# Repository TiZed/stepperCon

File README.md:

<b>stepperCon</b> is a PIC18F46K22 based stepper motor controller.

It was created as an exercise in controlling stepper motors for a CNC project. The board and firmware were designed to drive a L298P driver but can probably be adapted to other drivers.

'master' branch - Has hybrid PWM-analog current control. <br />
'a2d_pid' branch - Has the ADC PI current control, not stable yet.

Some of the feature of this project:
- Micro-stepping, selectable up to 16 micro-steps.
- Current limiting.
- I2C interface for configuration.
- Two indicator LEDs.

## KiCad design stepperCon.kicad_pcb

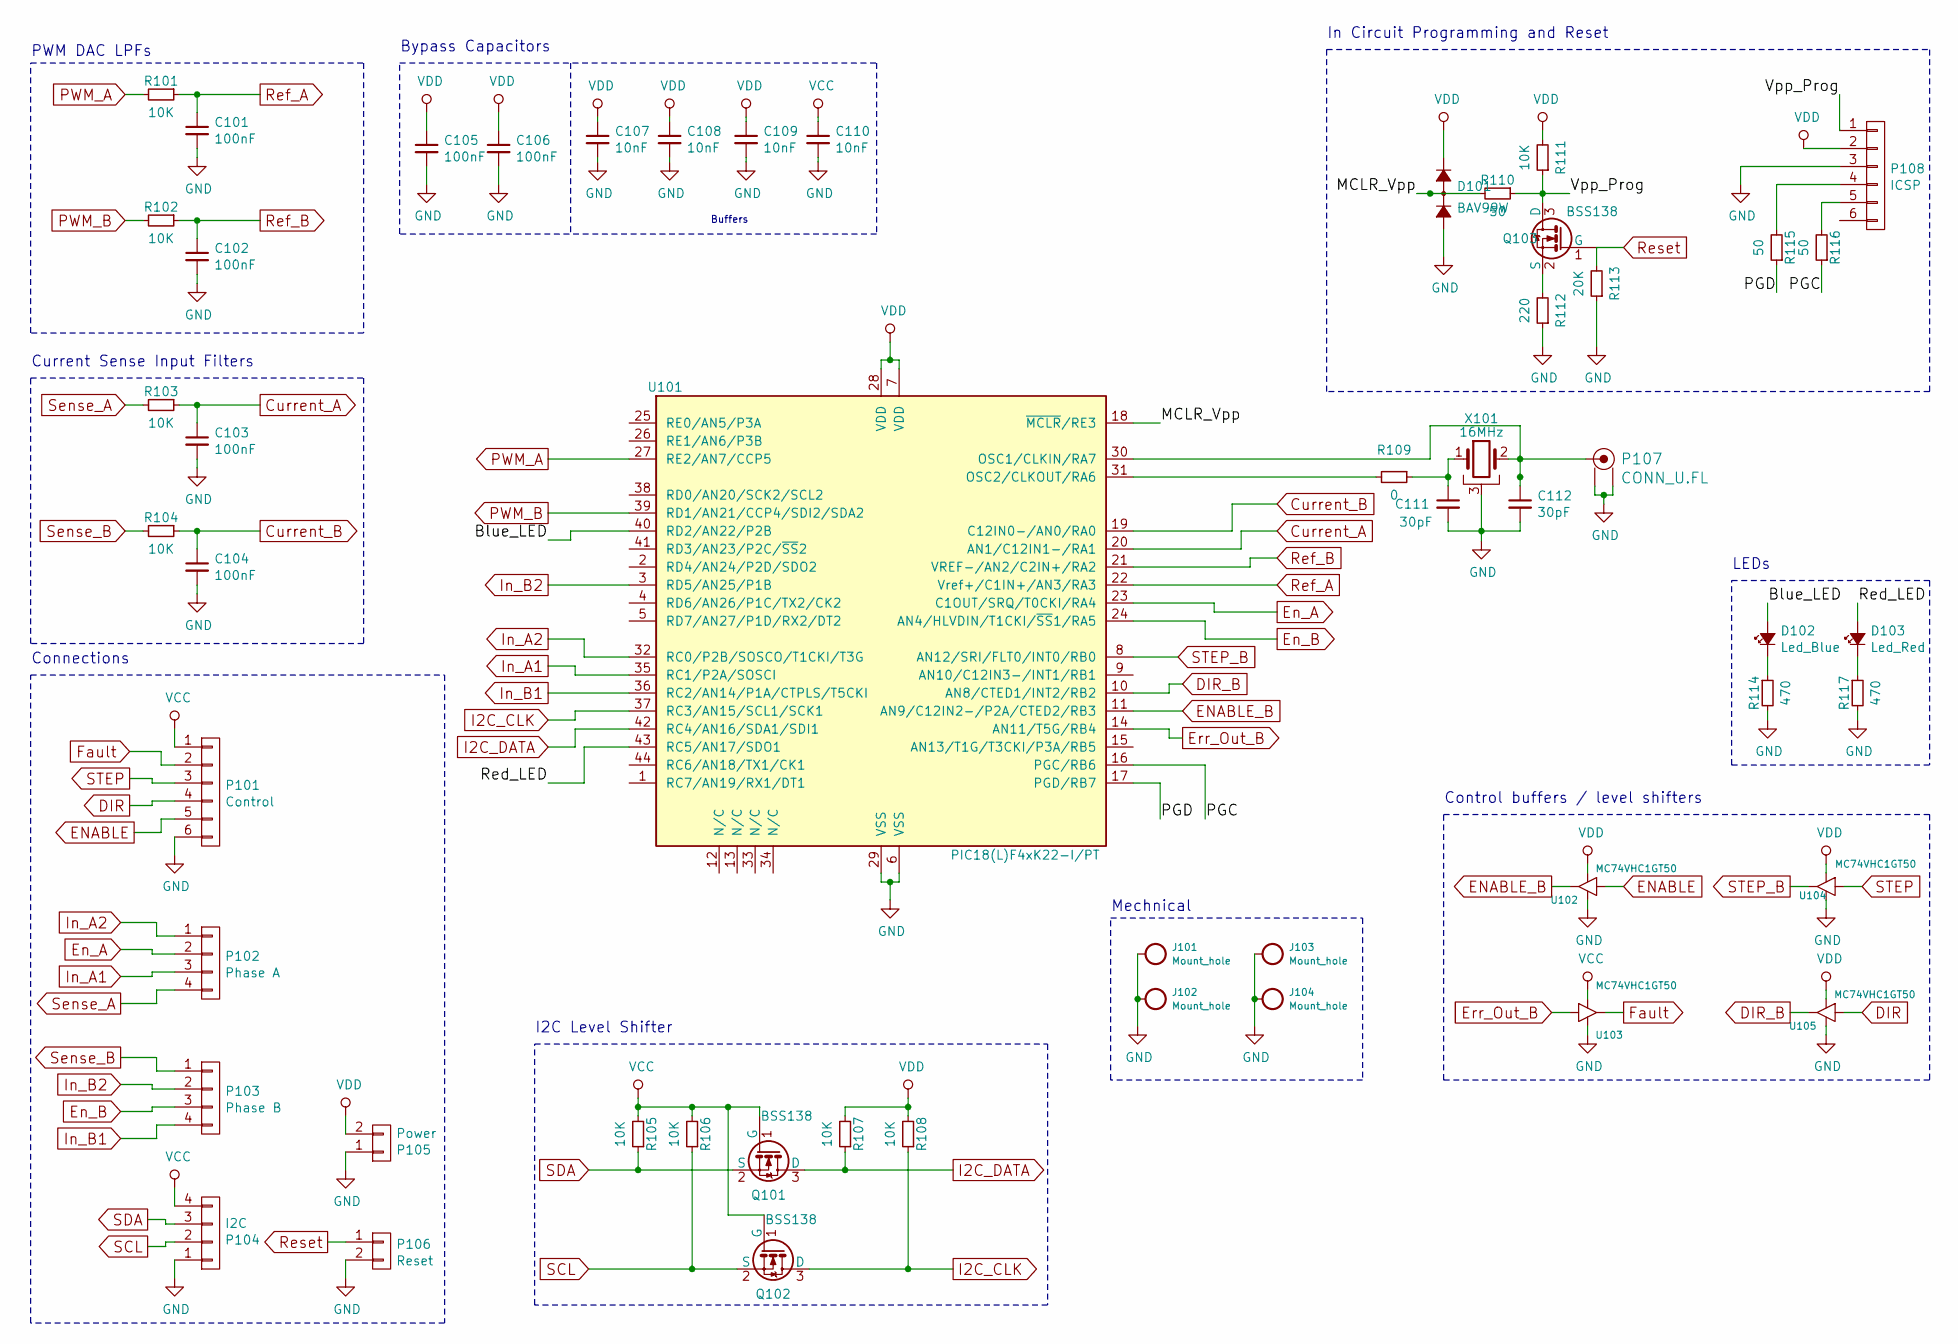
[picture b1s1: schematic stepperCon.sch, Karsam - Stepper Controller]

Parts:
C101, C102, C103, C104, C105, C106: 100nF; C_0603
C107, C108, C109, C110: 10nF; C_0603
C111, C112: 30pF; C_0603
D101: BAV99W; SOT-323
D102: Led_Blue; LED_0805
D103: Led_Red; LED_0805
J101, J102, J103, J104: Mount_hole; MountingHole_3.2mm_M3_Pad
P101: Control; Socket_Strip_Straight_1x06
P102: Phase A; Socket_Strip_Straight_1x04
P103: Phase B; Socket_Strip_Straight_1x04
P104: I2C; Socket_Strip_Straight_1x04
P105: Power; Socket_Strip_Straight_1x02
P106: Reset; Socket_Strip_Straight_1x02
P107: CONN_U.FL; UFL
P108: ICSP
Q101, Q102, Q103: BSS138; SOT-323
R101, R102, R103, R104, R105, R106, R107, R108, R111: 10K; R_0603
R109: 0; R_0603
R110, R115, R116: 50; R_0603
R112: 220; R_0603
R113: 20K; R_0603
R114, R117: 470; R_0603
U101: PIC18(L)F4xK22-I/PT; TQFP-44_10x10mm_Pitch0.8mm
U102, U103, U104, U105: MC74VHC1GT50; SOT-353
X101: 16MHz

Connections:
/Blue_LED: D102.2 (A), U101.40 (RD2/AN22/P2B)
/MCLR_Vpp: D101.3 (AK), R110.2, U101.18 (~MCLR~/RE3)
/PGC: R116.1, U101.16 (PGC/RB6)
/PGD: R115.1, U101.17 (PGD/RB7)
/Red_LED: D103.2 (A), U101.43 (RC5/AN17/SDO1)
/Vpp_Prog: P108.1, Q103.3 (D), R110.1, R111.1
Current_A: C103.1, R103.1, U101.20 (AN1/C12IN1-/RA1)
Current_B: C104.1, R104.1, U101.19 (C12IN0-/AN0/RA0)
DIR: P101.4, U105.2 (IN_A)
DIR_B: U101.10 (AN8/CTED1/INT2/RB2), U105.4 (OUT_Y)
ENABLE: P101.5, U102.2 (IN_A)
ENABLE_B: U101.11 (AN9/C12IN2-/P2A/CTED2/RB3), U102.4 (OUT_Y)
En_A: P102.2, U101.23 (C1OUT/SRQ/T0CKI/RA4)
En_B: P103.3, U101.24 (AN4/HLVDIN/T1CKI/~SS~1/RA5)
Err_Out_B: U101.14 (AN11/T5G/RB4), U103.2 (IN_A)
Fault: P101.2, U103.4 (OUT_Y)
GND: C101.2, C102.2, C103.2, C104.2, C105.2, C106.2, C107.2, C108.2, C109.2, C110.2, C111.2, C112.2, D101.1 (K), J101.1, J102.1, J103.1, J104.1, P101.6, P104.1, P105.1, P106.2, P107.2, P107.3, P108.3, R112.1, R113.1, R114.2, R117.2, U101.6 (VSS), U101.29 (VSS), U102.3 (GND), U103.3 (GND), U104.3 (GND), U105.3 (GND), X101.3
I2C_CLK: Q102.3 (D), R108.1, U101.37 (RC3/AN15/SCL1/SCK1)
I2C_DATA: Q101.3 (D), R107.1, U101.42 (RC4/AN16/SDA1/SDI1)
In_A1: P102.3, U101.35 (RC1/P2A/SOSCI)
In_A2: P102.1, U101.32 (RC0/P2B/SOSCO/T1CKI/T3G)
In_B1: P103.4, U101.36 (RC2/AN14/P1A/CTPLS/T5CKI)
In_B2: P103.2, U101.3 (RD5/AN25/P1B)
unnamed: C111.1, R109.1, X101.1
unnamed: C112.1, P107.1, U101.30 (OSC1/CLKIN/RA7), X101.2
unnamed: D102.1 (K), R114.1
unnamed: D103.1 (K), R117.1
unnamed: P108.4, R115.2
unnamed: P108.5, R116.2
unnamed: Q103.2 (S), R112.2
unnamed: R109.2, U101.31 (OSC2/CLKOUT/RA6)
PWM_A: R101.2, U101.27 (RE2/AN7/CCP5)
PWM_B: R102.2, U101.39 (RD1/AN21/CCP4/SDI2/SDA2)
Ref_A: C101.1, R101.1, U101.22 (Vref+/C1IN+/AN3/RA3)
Ref_B: C102.1, R102.1, U101.21 (VREF-/AN2/C2IN+/RA2)
Reset: P106.1, Q103.1 (G), R113.2
SCL: P104.2, Q102.2 (S), R106.1
SDA: P104.3, Q101.2 (S), R105.1
STEP: P101.3, U104.2 (IN_A)
STEP_B: U101.8 (AN12/SRI/FLT0/INT0/RB0), U104.4 (OUT_Y)
Sense_A: P102.4, R103.2
Sense_B: P103.1, R104.2
VCC: C110.1, P101.1, P104.4, Q101.1 (G), Q102.1 (G), R105.2, R106.2, U103.5 (VCC)
VDD: C105.1, C106.1, C107.1, C108.1, C109.1, D101.2 (A), P105.2, P108.2, R107.2, R108.2, R111.2, U101.7 (VDD), U101.28 (VDD), U102.5 (VCC), U104.5 (VCC), U105.5 (VCC)

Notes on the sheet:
I2C Level Shifter
PWM DAC LPFs
Current Sense Input Filters
Mechnical
Connections
Control buffers / level shifters
Bypass Capacitors
Buffers
LEDs
In Circuit Programming and Reset

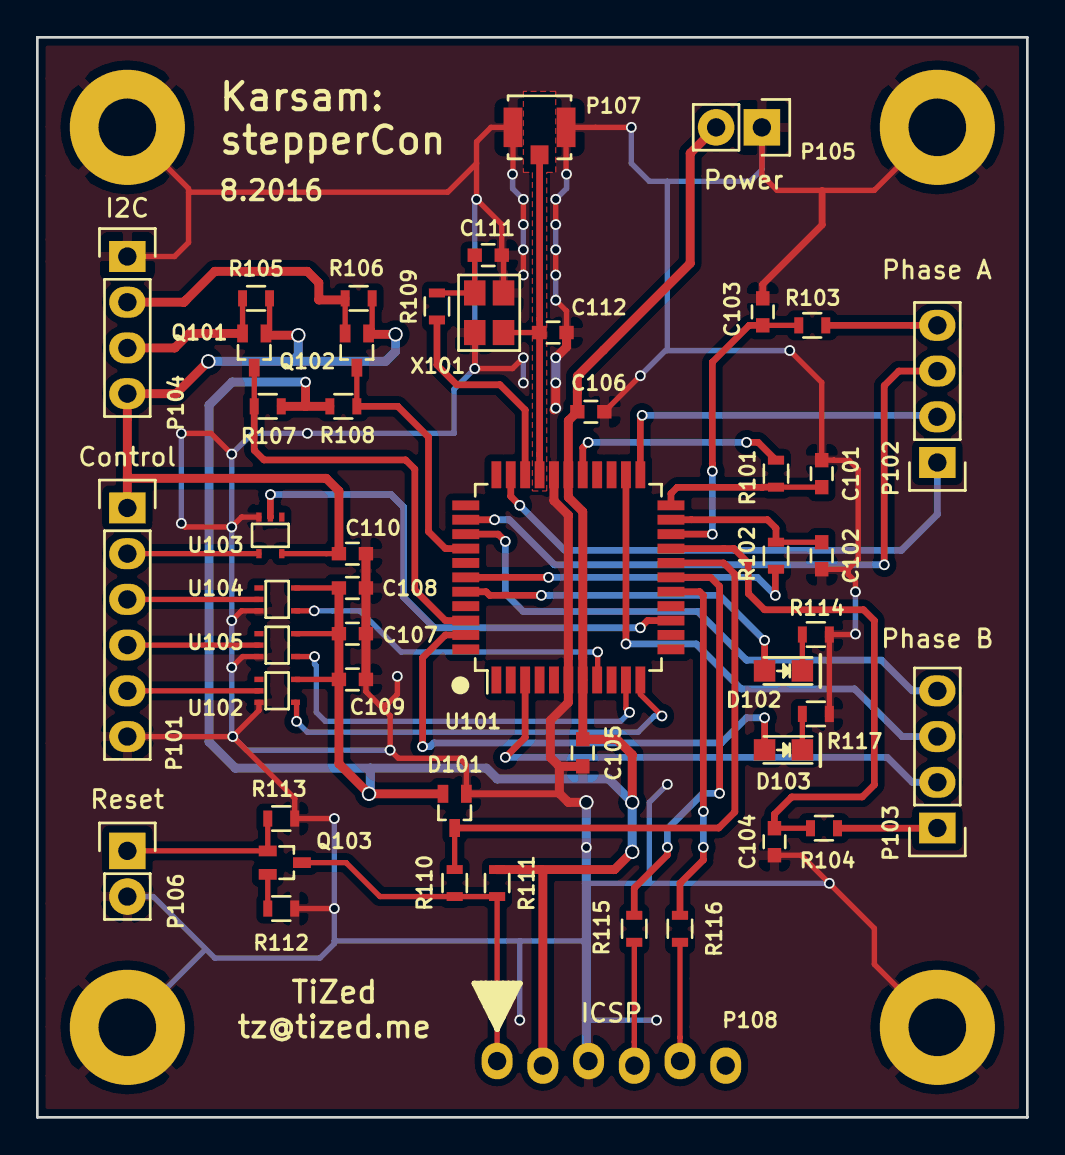
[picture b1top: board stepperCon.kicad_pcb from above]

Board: 2 copper layers, 55.0 x 60.0 mm, 53 parts (0 on the bottom side), 44 nets.

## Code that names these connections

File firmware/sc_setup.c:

/* 
 * File:   sc_setup.c
 * Author: TiZed
 *
 * Created on 12 August 2016
 * 
 *  Copyright (C) 2016 TiZed
 *
 *  This program is free software: you can redistribute it and/or modify
 *  it under the terms of the GNU General Public License as published by
 *  the Free Software Foundation, either version 3 of the License, or
 *  (at your option) any later version.
 *
 *  This program is distributed in the hope that it will be useful,
 *  but WITHOUT ANY WARRANTY; without even the implied warranty of
 *  MERCHANTABILITY or FITNESS FOR A PARTICULAR PURPOSE.  See the
 *  GNU General Public License for more details.
 *
 *  You should have received a copy of the GNU General Public License
 *  along with this program.  If not, see <http://www.gnu.org/licenses/>.
 *
 * ----------------------------------------------------------------------------
 * 
 */

#include <pic18fregs.h>
#include <stdint.h>

#define TMR_10MS  45535

void ioSetup(void) {
    TRISBbits.RB4 = 0 ;     // Start with a cleared 'fault' signal
    PORTBbits.RB4 = 0 ;
    
    ANSELDbits.ANSD2 = 0 ;
    TRISDbits.RD2 = 0 ;     // Start with blue LED off
    PORTDbits.RD2 = 0 ;
    
    ANSELC = 0x00 ;         // Disable Port-C as analog input
   
    TRISCbits.RC5 = 0 ;     // Start with red LED off
    PORTCbits.RC5 = 0 ;
    
    TRISAbits.RA4 = 0 ;
    LATAbits.LATA4 = 0 ;
    
    ANSELAbits.ANSA5 = 0 ;
    TRISAbits.RA5 = 0 ;
    LATAbits.LATA5 = 0 ;
    
    ANSELB = 0x00 ;         // Disable port B analog input
    
    ANSELDbits.ANSD5 = 0 ;  
   
    TRISBbits.RB0 = 1 ;     // 'step', 'dir' and 'enable' as inputs
    TRISBbits.RB2 = 1 ;
    TRISBbits.RB3 = 1 ;
}

void pwmSetup(uint8_t db_time) {
    // ECCP2 - Phase A PWM 
    // ECCP1 - Phase B PWM
    
    TRISCbits.TRISC0 = 1 ;          // Disable port drivers for setup
    TRISCbits.TRISC1 = 1 ;
    TRISCbits.TRISC2 = 1 ;
    TRISDbits.TRISD5 = 1 ;
    TRISDbits.TRISD1 = 1 ;
    TRISEbits.TRISE2 = 1 ;
    
    CCPTMRS0bits.C2TSEL = 0b10 ;    // Timer6 to ECCP2
    CCPTMRS0bits.C1TSEL = 0b10 ;    // Timer6 to ECCP1  
    CCPTMRS1bits.C5TSEL = 0b01 ;    // Timer4 to CCP5
    CCPTMRS1bits.C4TSEL = 0b01 ;    // Timer4 to CCP4
    
    T6CONbits.TMR6ON = 0 ;          // Turn Timer6 off
    PR6 = 0xff ;                    // Set Timer6 for 62.5kHz (15.625kHz) @64MHz, 10-bit res
    T6CONbits.T6CKPS = 0b01 ;       // Set prescaler to 1:1 (0b01 = 1:4)
    
    T4CONbits.TMR4ON = 0 ;          // Turn Timer4 off
    PR4 = 0xff ;                    // Set Timer4 for 62.5kHz @64MHz, 10-bit res
    T4CONbits.T4CKPS = 0b00 ;       // Set prescaler to 1:1
    
    ECCP2ASbits.PSS2AC = 0b00  ;    // Pin A1 set to '0' at shutdown
    ECCP2ASbits.PSS2BD = 0b00  ;    // Pin A2 set to '0' at shutdown
    ECCP1ASbits.PSS1AC = 0b00  ;    // Pin B1 set to '0' at shutdown
    ECCP1ASbits.PSS1BD = 0b00  ;    // Pin B2 set to '0' at shutdown
    
    ECCP2ASbits.CCP2AS = 0x00  ;    // Disable auto-shutdown
    ECCP1ASbits.CCP1AS = 0x00  ;    
    
    ECCP2ASbits.CCP2ASE = 1    ;    // Force shutdown
    ECCP1ASbits.CCP1ASE = 1    ;    
    
    CCP2CONbits.P2M = 0b10 ;
    CCP2CONbits.CCP2M = 0b1111 ;    // Phase A Half-bridge mode 
    CCP1CONbits.P1M = 0b10 ;
    CCP1CONbits.CCP1M = 0b1111 ;    // Phase B Half-bridge mode
    
    CCP5CONbits.CCP5M = 0b1100 ;    // A Ref PWM
    CCP4CONbits.CCP4M = 0b1100 ;    // B Ref PWM
    
    PWM2CONbits.P2DC = db_time ;    // 16 * 4 * Tosc = 1us dead-band
    PWM1CONbits.P1DC = db_time ; 
    
    TRISCbits.TRISC0 = 0 ;          // Enable port drivers
    TRISCbits.TRISC1 = 0 ;
    TRISCbits.TRISC2 = 0 ;
    TRISDbits.TRISD5 = 0 ;
    TRISDbits.TRISD1 = 0 ;
    TRISEbits.TRISE2 = 0 ;
    
    CCPR2L = 128 ;
    CCP2CONbits.DC2B = 0 ;
    
    CCPR1L = 128 ;
    CCP1CONbits.DC1B = 0 ;
            
    CCPR5L = 32 ;
    CCP5CONbits.DC5B = 0 ;
    
    CCPR4L = 32 ;
    CCP4CONbits.DC4B = 0 ;
    
    T6CONbits.TMR6ON = 1 ;          // Start PWM timer
    T4CONbits.TMR4ON = 1 ;          // Start PWM timer
    
    ECCP2ASbits.CCP2ASE = 0    ;    // Enable PWM
    ECCP1ASbits.CCP1ASE = 0    ;    
}

void compsSetup(void) {
    // Comparator 1 (Phase A) setup
    CM1CON0bits.C1CH = 0b01 ;       // C12N1- input to C1-
    CM1CON0bits.C1R = 0 ;           // C1+ to RA3
    CM2CON1bits.C1RSEL = 0 ;        // Use DAC as Vref
    CM1CON0bits.C1POL = 1 ;         // Invert logic
    CM1CON0bits.C1SP = 1 ;          // Normal power, high speed mode
    CM2CON1bits.C1HYS = 0 ;         // Enable hysteresis
    
    // Comparator 2 (Phase B) setup
    CM2CON0bits.C2CH = 0b00 ;       // C12N0- input to C2-
    CM2CON0bits.C2R = 0 ;           // C2+ to RA2
    CM2CON1bits.C2RSEL = 0 ;        // Use DAC as Vref
    CM2CON0bits.C2POL = 1 ;         // Invert logic
    CM2CON0bits.C2SP = 1 ;          // Normal power, high speed mode
    CM2CON1bits.C2HYS = 0 ;         // Enable hysteresis
    
    PIR2bits.C1IF = 0 ;             // Clear any pending interrupts 
    PIR2bits.C2IF = 0 ; 
    
    CM1CON0bits.C1ON = 1 ;          // Enable comparator 1
    CM2CON0bits.C2ON = 1 ;          // Enable comparator 2
}

void intSetup(void) {
    INTCONbits.GIE_GIEH = 0 ;   // Disable interrupts
    INTCONbits.PEIE_GIEL = 0 ;
    
    RCONbits.IPEN = 1 ;         // Enable interrupts priority

    INTCON2bits.RBPU = 1 ;      // Disable Port B pull-ups
    INTCON2bits.INTEDG0 = 1 ;   // 'step' interrupt on rising edge
    
    INTCON3bits.INT2IP = 0 ;    // Low priority to 'dir' interrupt
    IPR1bits.ADIP = 1 ;         // ADC High priority interrupt
    IPR1bits.SSP1IP = 0 ;       // Low priority to I2C interrupt
    
    IPR2bits.C1IP = 1 ;         // Set comparators interrupts to high priority
    IPR2bits.C2IP = 1 ;
    
    INTCONbits.GIE_GIEH = 1 ;   // Enable interrupts
    INTCONbits.PEIE_GIEL = 1 ;
}

// Setup ADC for current capture
void adc_setup(void) {
    ADCON0bits.ADON = 0 ;      // ADC Off
    
    ADCON2bits.ADCS = 0b110 ;  // ADC clock = Fosc/64 = 1us
    ADCON2bits.ACQT = 0b101 ;  // 12 Tad acquisition time
    ADCON2bits.ADFM = 1 ; 
    
    ADCON1bits.PVCFG = 0b00 ;  // Pos. Ref. voltage = AVdd
    ADCON1bits.NVCFG = 0b00 ;  // Nrg. Ref. voltage = AVss
    ADCON1bits.TRIGSEL = 1  ;  // Set GO trigger to CCP5
    
    TRISAbits.TRISA0 = 1 ;
    ANSELAbits.ANSA0 = 1 ;     // Enable RA0 as analog input
    
    TRISAbits.TRISA1 = 1 ;
    ANSELAbits.ANSA1 = 1 ;     // Enable RA1 as analog input
    
    PIR1bits.ADIF = 0 ;        // Reset ADC interrupt 
    PIE1bits.ADIE = 0 ;        // Disable ADC interrupt
    
    ADCON0bits.ADON = 1 ;      // ADC On
}

void resetCheck(void) {
    uint8_t i ;
    
    // On WDT timeout, Power down detect or brown-out
    if(!RCONbits.TO || !RCONbits.PD || !RCONbits.BOR) {
        // Reset RCON flags
        RCONbits.TO = 1 ;
        RCONbits.PD = 1 ;
        RCONbits.BOR = 0 ;
        RCONbits.POR = 0 ;

        PORTBbits.RB4 = 1 ;     // Rise 'fault' signal
        PORTCbits.RC5 = 1 ;     // Turn on red LED

        while(1) ; 
    }

    // On stack over/underflow
    if(STKPTRbits.STKFUL || STKPTRbits.STKUNF) {
        // Clear stack pointer flags
        STKPTRbits.STKFUL = 0 ;
        STKPTRbits.STKUNF = 0 ;

        PORTBbits.RB4 = 1 ;     // Rise 'fault' signal
        PORTCbits.RC5 = 1 ;     // Turn on red LED

        // Blink RED LED
        T1CONbits.TMR1CS = 0 ;      // Timer1 to Fosc/4
        i = 120 ;

        while(1) {
            T1CONbits.TMR1ON = 0 ;
            PIR1bits.TMR1IF = 0 ;
            T1CONbits.T1CKPS = 3 ;      // Timer1 1:8 prescale
            TMR1H = TMR_10MS >> 8 ;
            TMR1L = TMR_10MS ;
            T1CONbits.TMR1ON = 1 ;

            while(!PIR1bits.TMR1IF) ;

            if (--i == 0) {
                LATCbits.LATC5 = !LATCbits.LATC5 ;
                i = 120 ;
            }
        }
    }
}

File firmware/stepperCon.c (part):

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
    ADCON0bits.GO = 0 ;

    PORTDbits.RD2 = 0 ;             // Turn blue LED off
    state = IDLE ;
}

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}

int main(void) {
    int16_t pwm_a = 0, pwm_b = 0 ;
    uint16_t adc_res ;
    pi_result_t pi_result_a ;
    pi_result_t pi_result_b ;   
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    uint16_t adc_wdt ; 
  
    int16_t step_a = 0 ;                         // Current phase A step
    int16_t step_b = 0 ;                         // Current phase B step
    
    ioSetup() ;                 // Setup IO ports
    
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    state = IDLE ;              // Start in 'idle' state
    
    // Blink Blue LED once - indicate ready
    PORTDbits.RD2 = 1 ;     // Turn blue LED on
    delay_ms(300) ;    
    PORTDbits.RD2 = 0 ;     // Turn blue LED off
    
    WDTCON = 1 ;        // Enable watchdog timer
    
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
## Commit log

2017-12-08 Changed to 8 microstepping default
2017-12-09 Selectable microstepping
2018-02-09 Some comments to the code
2018-04-13 Adjusted current limit
2018-04-14 ADC setup and capture. Half-bridge PWM setup.
2018-09-08 First commit of working PI, with simulation Jupyter notebook.
2018-10-10 PI disabled until stabilized, more simulation code
2018-10-10 Updated branch descriptions.
2018-10-10 Fixed readme formating
